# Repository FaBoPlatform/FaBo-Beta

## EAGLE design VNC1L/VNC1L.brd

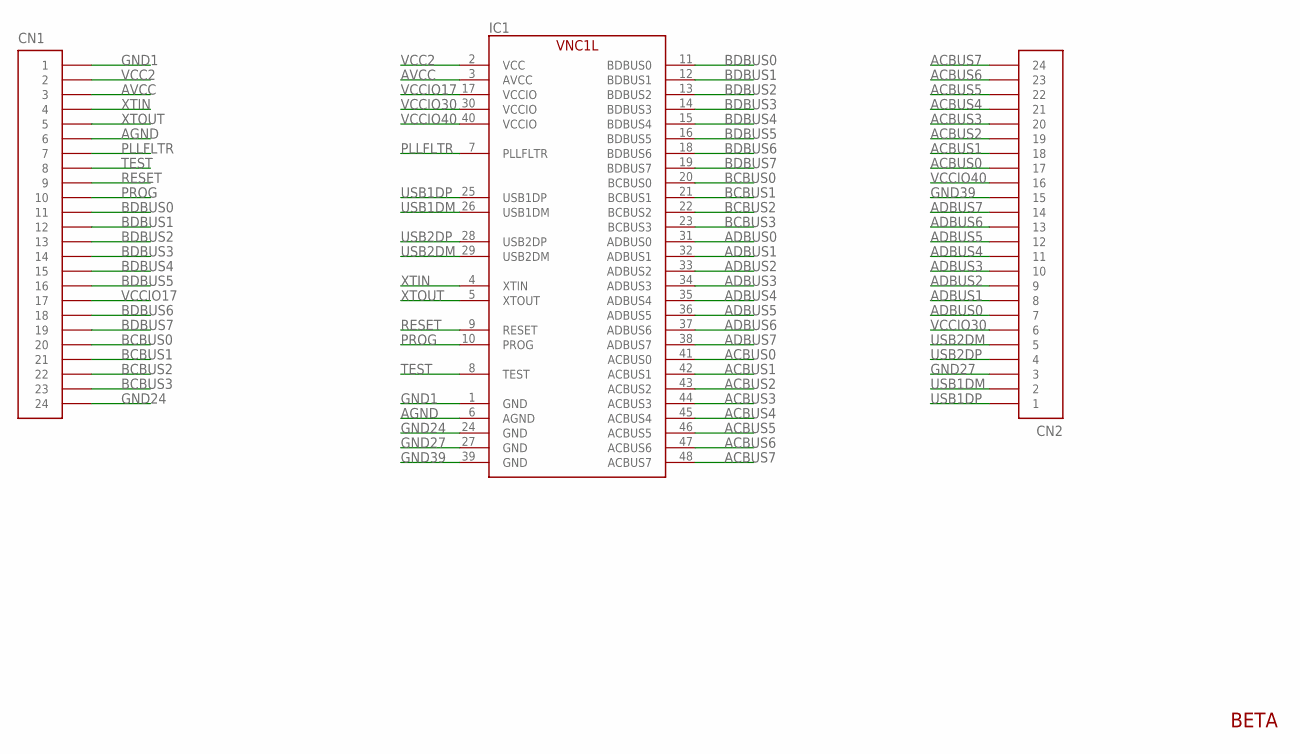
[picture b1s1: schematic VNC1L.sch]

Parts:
CN1, CN2: PIN_HEADER_1X24; PIN_1X24_SNEAKY
IC1: VNC1L-1A; LQFP-48

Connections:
ACBUS0: CN2.17, IC1.41 (ACBUS0)
ACBUS1: CN2.18, IC1.42 (ACBUS1)
ACBUS2: CN2.19, IC1.43 (ACBUS2)
ACBUS3: CN2.20, IC1.44 (ACBUS3)
ACBUS4: CN2.21, IC1.45 (ACBUS4)
ACBUS5: CN2.22, IC1.46 (ACBUS5)
ACBUS6: CN2.23, IC1.47 (ACBUS6)
ACBUS7: CN2.24, IC1.48 (ACBUS7)
ADBUS0: CN2.7, IC1.31 (ADBUS0)
ADBUS1: CN2.8, IC1.32 (ADBUS1)
ADBUS2: CN2.9, IC1.33 (ADBUS2)
ADBUS3: CN2.10, IC1.34 (ADBUS3)
ADBUS4: CN2.11, IC1.35 (ADBUS4)
ADBUS5: CN2.12, IC1.36 (ADBUS5)
ADBUS6: CN2.13, IC1.37 (ADBUS6)
ADBUS7: CN2.14, IC1.38 (ADBUS7)
AGND: CN1.6, IC1.6 (AGND)
AVCC: CN1.3, IC1.3 (AVCC)
BCBUS0: CN1.20, IC1.20 (BCBUS0)
BCBUS1: CN1.21, IC1.21 (BCBUS1)
BCBUS2: CN1.22, IC1.22 (BCBUS2)
BCBUS3: CN1.23, IC1.23 (BCBUS3)
BDBUS0: CN1.11, IC1.11 (BDBUS0)
BDBUS1: CN1.12, IC1.12 (BDBUS1)
BDBUS2: CN1.13, IC1.13 (BDBUS2)
BDBUS3: CN1.14, IC1.14 (BDBUS3)
BDBUS4: CN1.15, IC1.15 (BDBUS4)
BDBUS5: CN1.16, IC1.16 (BDBUS5)
BDBUS6: CN1.18, IC1.18 (BDBUS6)
BDBUS7: CN1.19, IC1.19 (BDBUS7)
GND1: CN1.1, IC1.1 (GND)
GND24: CN1.24, IC1.24 (GND)
GND27: CN2.3, IC1.27 (GND)
GND39: CN2.15, IC1.39 (GND)
PLLFLTR: CN1.7, IC1.7 (PLLFLTR)
PROG: CN1.10, IC1.10 (PROG)
RESET: CN1.9, IC1.9 (RESET)
TEST: CN1.8, IC1.8 (TEST)
USB1DM: CN2.2, IC1.26 (USB1DM)
USB1DP: CN2.1, IC1.25 (USB1DP)
USB2DM: CN2.5, IC1.29 (USB2DM)
USB2DP: CN2.4, IC1.28 (USB2DP)
VCC2: CN1.2, IC1.2 (VCC)
VCCIO17: CN1.17, IC1.17 (VCCIO)
VCCIO30: CN2.6, IC1.30 (VCCIO)
VCCIO40: CN2.16, IC1.40 (VCCIO)
XTIN: CN1.4, IC1.4 (XTIN)
XTOUT: CN1.5, IC1.5 (XTOUT)

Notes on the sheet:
BETA

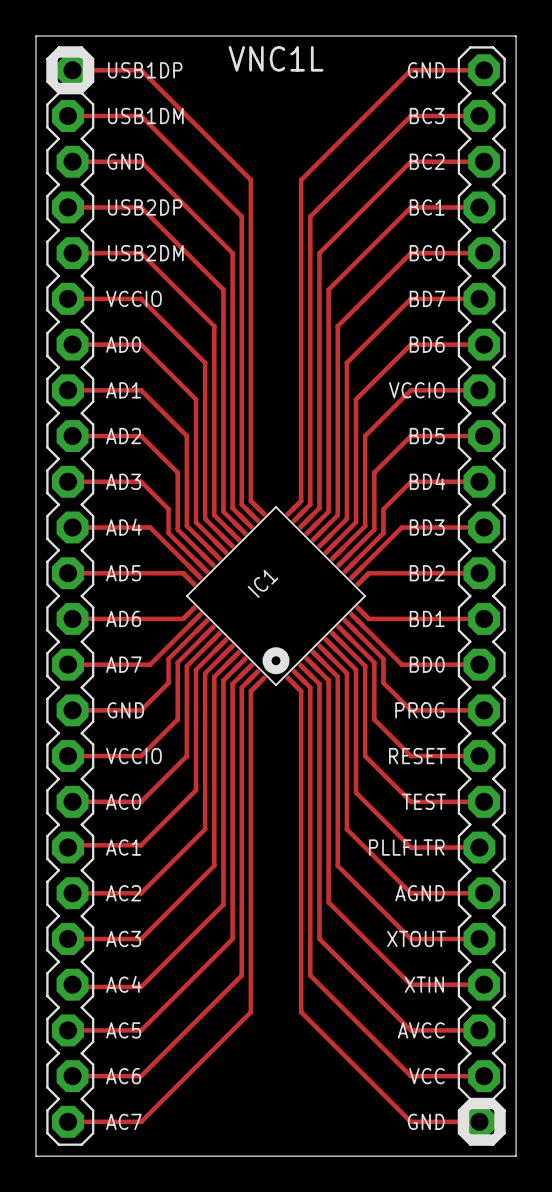
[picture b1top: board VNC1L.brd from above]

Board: 2 copper layers, 26.7 x 62.2 mm, 3 parts (0 on the bottom side), 48 nets.

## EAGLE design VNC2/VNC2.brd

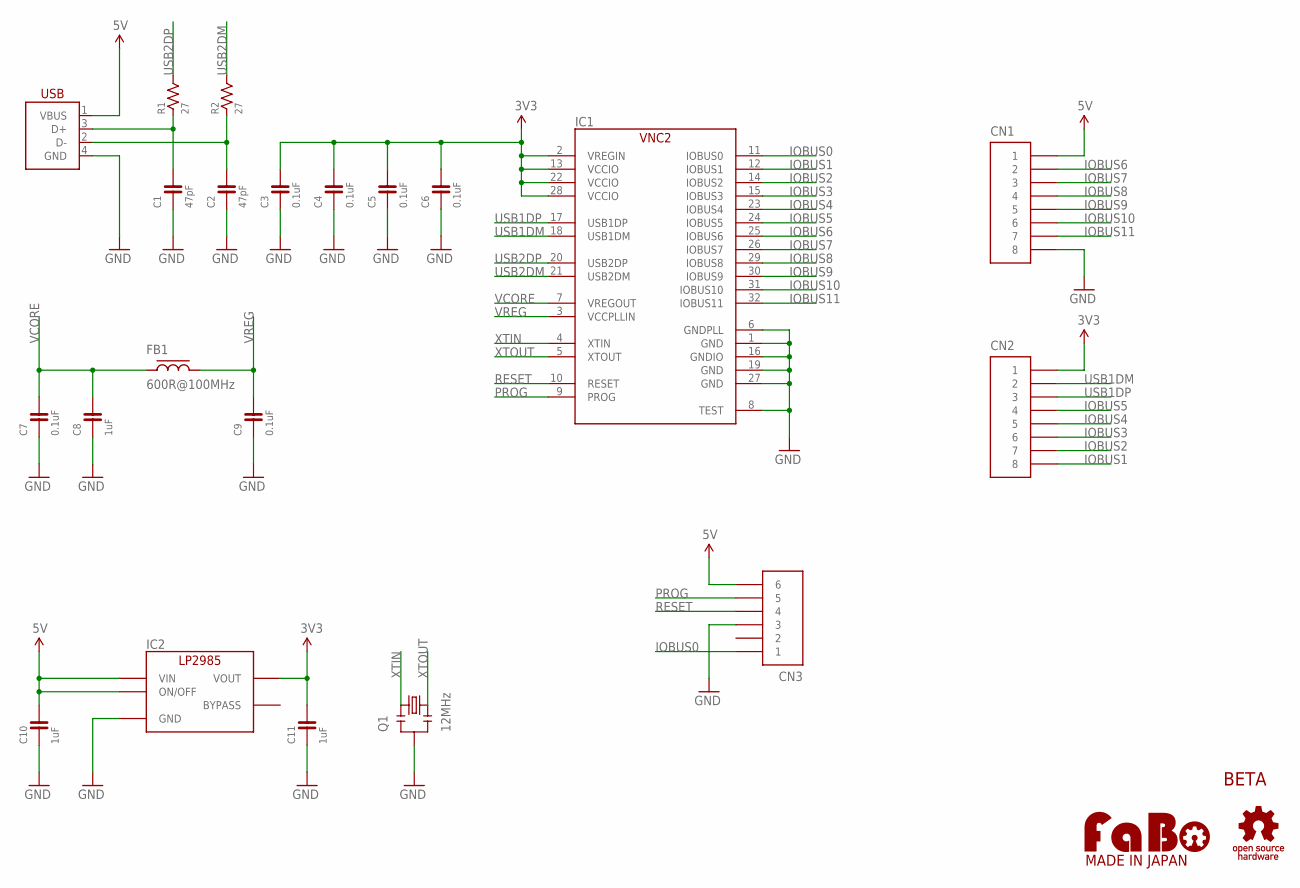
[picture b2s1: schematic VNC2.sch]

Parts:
C1, C2: 47pF; 0603-NARROW
C3, C4, C5, C6, C7, C9: 0.1uF; 0603-NARROW
C8, C10, C11: 1uF; 0603-NARROW
CN1, CN2: PIN_HEADER_1X8-SNEAKY; PIN_1X8_SNEAKY
CN3: PIN_HEADER_1X6-SNEAKY; PIN_1X6_SNEAKY
FB1: 600R@100MHz; EIA0603
IC1: VNC2-32Q1B; QFN-32_VNC2
IC2: LP2985-33DBV; SOT-23-5
Q1: 12MHz; CSTCE_G
R1, R2: 27; 0603-NARROW
U$2: LOGO_FABO-S_BOTTOM; LOGO_FABO_S_BOTTOM
U$3: LOGO_OSHW-S_BOTTOM; LOGO_OSHW_S_BOTTOM
USB1: USB-B_PTH; USB-4AF103BS

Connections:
3V3: C3.2, C4.2, C5.2, C6.2, C11.2, CN2.1, IC1.2 (VREGIN), IC1.13 (VCCIO), IC1.22 (VCCIO), IC1.28 (VCCIO), IC2.5 (VOUT)
5V: C10.2, CN1.1, CN3.6, IC2.1 (VIN), IC2.3 (ON/OFF), USB1.1 (VBUS)
GND: C1.1, C2.1, C3.1, C4.1, C5.1, C6.1, C7.1, C8.1, C9.1, C10.1, C11.1, CN1.8, CN3.3, IC1.1 (GND), IC1.6 (GNDPLL), IC1.8 (TEST), IC1.16 (GNDIO), IC1.19 (GND), IC1.27 (GND), IC2.2 (GND), Q1.2, USB1.4 (GND)
IOBUS0: CN3.1, IC1.11 (IOBUS0)
IOBUS1: CN2.8, IC1.12 (IOBUS1)
IOBUS2: CN2.7, IC1.14 (IOBUS2)
IOBUS3: CN2.6, IC1.15 (IOBUS3)
IOBUS4: CN2.5, IC1.23 (IOBUS4)
IOBUS5: CN2.4, IC1.24 (IOBUS5)
IOBUS6: CN1.2, IC1.25 (IOBUS6)
IOBUS7: CN1.3, IC1.26 (IOBUS7)
IOBUS8: CN1.4, IC1.29 (IOBUS8)
IOBUS9: CN1.5, IC1.30 (IOBUS9)
IOBUS10: CN1.6, IC1.31 (IOBUS10)
IOBUS11: CN1.7, IC1.32 (IOBUS11)
unnamed: C1.2, R1.1, USB1.3 (D+)
unnamed: C2.2, R2.1, USB1.2 (D-)
PROG: CN3.5, IC1.9 (PROG)
RESET: CN3.4, IC1.10 (RESET)
USB1DM: CN2.2, IC1.18 (USB1DM)
USB1DP: CN2.3, IC1.17 (USB1DP)
USB2DM: IC1.21 (USB2DM), R2.2
USB2DP: IC1.20 (USB2DP), R1.2
VCORE: C7.2, C8.2, FB1.1, IC1.7 (VREGOUT)
VREG: C9.2, FB1.2, IC1.3 (VCCPLLIN)
XTIN: IC1.4 (XTIN), Q1.1
XTOUT: IC1.5 (XTOUT), Q1.3

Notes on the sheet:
BETA

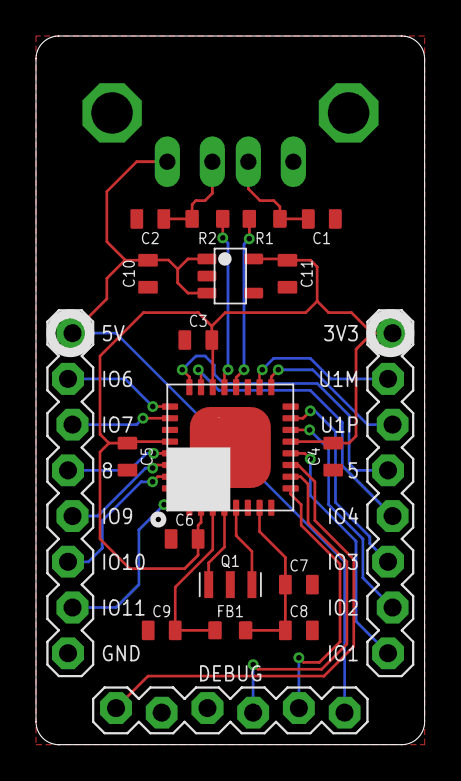
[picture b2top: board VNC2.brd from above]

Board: 2 copper layers, 21.6 x 39.4 mm, 23 parts (0 on the bottom side), 27 nets.

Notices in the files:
parts and their libraries:
FaBo-PIN: Released under the Creative Commons Attribution-ShareAlike 4.0 License
https://creativecommons.org/licenses/by-sa/4.0
FaBo-etc: Released under the Creative Commons
